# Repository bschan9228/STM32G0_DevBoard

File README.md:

# STM32G0 DevBoard
The STM32G0 DevBoard is a devlopment board based on the STM32G070CBT6. It has a USB Type C connector that only supports power and ST-LINK to program the device. It also contains buttons, LEDs, an external oscillator, and a linear regulator.

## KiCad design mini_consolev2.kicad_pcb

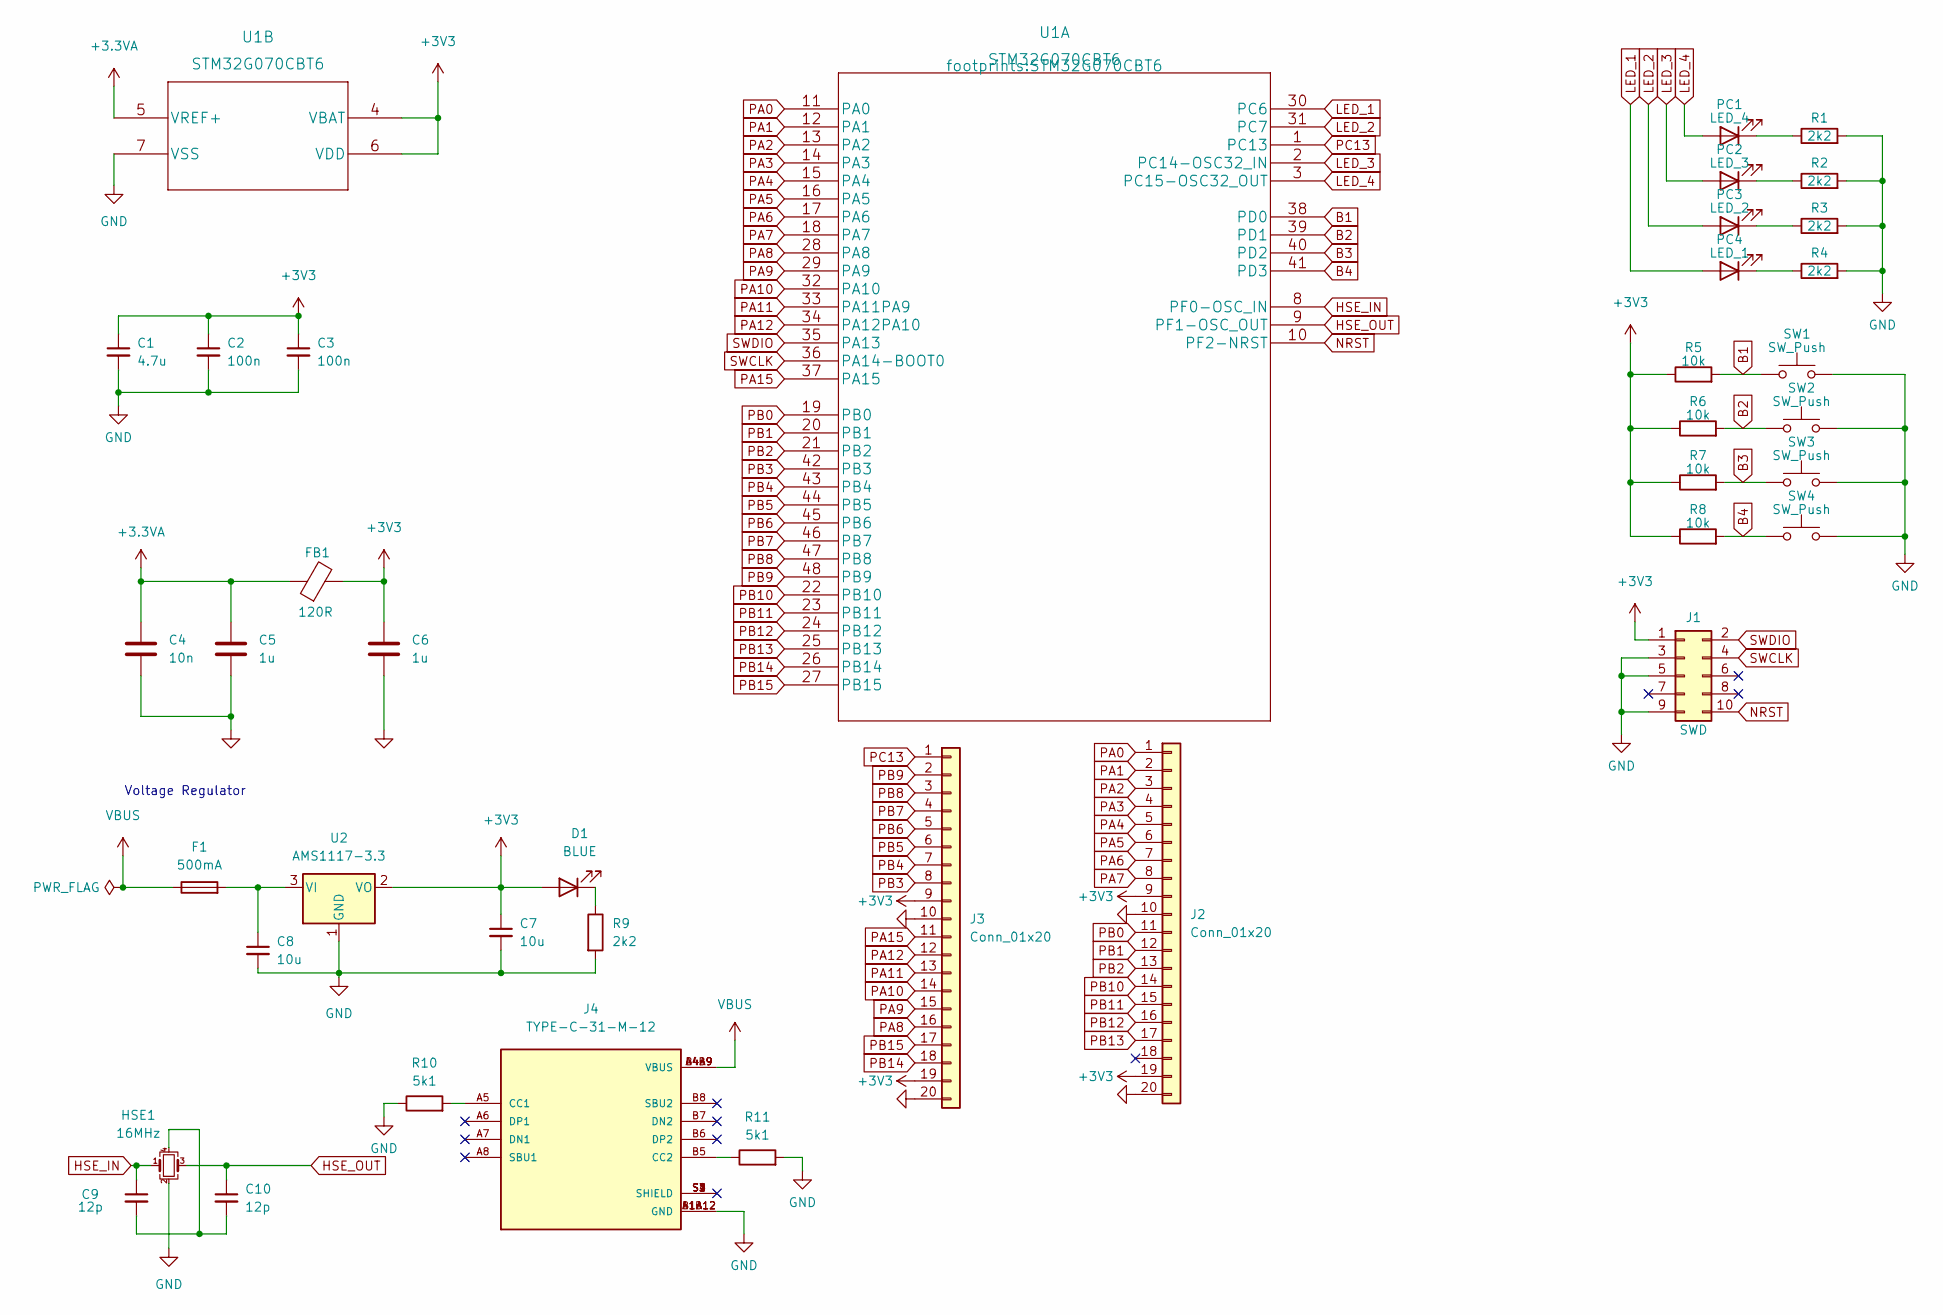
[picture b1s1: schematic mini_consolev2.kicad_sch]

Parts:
C1: 4.7u; C_0603_1608Metric
C2, C3: 100n; C_0402_1005Metric
C4: 10n; C_0402_1005Metric
C5, C6: 1u; C_0402_1005Metric
C7, C8: 10u; C_0603_1608Metric
C9, C10: 12p; C_0402_1005Metric
D1: BLUE; LED_0603_1608Metric
F1: 500mA; Fuse_0603_1608Metric
FB1: 120R; L_0603_1608Metric
HSE1: 16MHz; Crystal_SMD_3225-4Pin_3.2x2.5mm
J1: SWD; PinHeader_2x05_P2.54mm_Vertical
J2, J3: Conn_01x20; PinHeader_1x20_P1.27mm_Vertical
J4: TYPE-C-31-M-12; HRO_TYPE-C-31-M-12; PARTREV A
PC1: LED_4; LED_0603_1608Metric
PC2: LED_3; LED_0603_1608Metric
PC3: LED_2; LED_0603_1608Metric
PC4: LED_1; LED_0603_1608Metric
R1, R2, R3, R4, R9: 2k2; R_0402_1005Metric
R5, R6, R7, R8: 10k; R_0402_1005Metric
R10, R11: 5k1; R_0402_1005Metric
SW1, SW2, SW3, SW4: SW_Push; SW_PUSH_6mm_H5mm
U1: STM32G070CBT6
U2: AMS1117-3.3; SOT-223-3_TabPin2

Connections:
+3.3VA: C4.1, C5.1, FB1.1, U1.5 (VREF+)
+3V3: C1.1, C2.1, C3.1, C6.1, C7.1, D1.2 (A), FB1.2, J1.1, J2.9, J2.19, J3.9, J3.19, R5.1, R6.1, R7.1, R8.1, U1.4 (VBAT), U1.6 (VDD), U2.2 (VO)
B1: R5.2, SW1.1, U1.38 (PD0)
B2: R6.2, SW2.1, U1.39 (PD1)
B3: R7.2, SW3.1, U1.40 (PD2)
B4: R8.2, SW4.1, U1.41 (PD3)
GND: C1.2, C2.2, C3.2, C4.2, C5.2, C6.2, C7.2, C8.2, HSE1.2, J1.3, J1.5, J1.9, J2.10, J2.20, J3.10, J3.20, J4.A1B12 (GND), J4.B1A12 (GND), R1.2, R2.2, R3.2, R4.2, R9.2, R10.1, R11.2, SW1.2, SW2.2, SW3.2, SW4.2, U1.7 (VSS), U2.1 (GND)
HSE_IN: C9.1, HSE1.1, U1.8 (PF0-OSC_IN)
HSE_OUT: C10.1, HSE1.3, U1.9 (PF1-OSC_OUT)
LED_1: PC4.2 (A), U1.30 (PC6)
LED_2: PC3.2 (A), U1.31 (PC7)
LED_3: PC2.2 (A), U1.2 (PC14-OSC32_IN)
LED_4: PC1.2 (A), U1.3 (PC15-OSC32_OUT)
NRST: J1.10, U1.10 (PF2-NRST)
unnamed: C8.1, F1.2, U2.3 (VI)
unnamed: C9.2, C10.2, HSE1.4
unnamed: D1.1 (K), R9.1
unnamed: J4.A5 (CC1), R10.2
unnamed: J4.B5 (CC2), R11.1
unnamed: PC1.1 (K), R1.1
unnamed: PC2.1 (K), R2.1
unnamed: PC3.1 (K), R3.1
unnamed: PC4.1 (K), R4.1
PA0: J2.1, U1.11 (PA0)
PA1: J2.2, U1.12 (PA1)
PA2: J2.3, U1.13 (PA2)
PA3: J2.4, U1.14 (PA3)
PA4: J2.5, U1.15 (PA4)
PA5: J2.6, U1.16 (PA5)
PA6: J2.7, U1.17 (PA6)
PA7: J2.8, U1.18 (PA7)
PA8: J3.16, U1.28 (PA8)
PA9: J3.15, U1.29 (PA9)
PA10: J3.14, U1.32 (PA10)
PA11: J3.13, U1.33 (PA11PA9)
PA12: J3.12, U1.34 (PA12PA10)
PA15: J3.11, U1.37 (PA15)
PB0: J2.11, U1.19 (PB0)
PB1: J2.12, U1.20 (PB1)
PB2: J2.13, U1.21 (PB2)
PB3: J3.8, U1.42 (PB3)
PB4: J3.7, U1.43 (PB4)
PB5: J3.6, U1.44 (PB5)
PB6: J3.5, U1.45 (PB6)
PB7: J3.4, U1.46 (PB7)
PB8: J3.3, U1.47 (PB8)
PB9: J3.2, U1.48 (PB9)
PB10: J2.14, U1.22 (PB10)
PB11: J2.15, U1.23 (PB11)
PB12: J2.16, U1.24 (PB12)
PB13: J2.17, U1.25 (PB13)
PB14: J3.18, U1.26 (PB14)
PB15: J3.17, U1.27 (PB15)
PC13: J3.1, U1.1 (PC13)
SWCLK: J1.4, U1.36 (PA14-BOOT0)
SWDIO: J1.2, U1.35 (PA13)
VBUS: F1.1, J4.A4B9 (VBUS), J4.B4A9 (VBUS)

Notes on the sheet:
Voltage Regulator

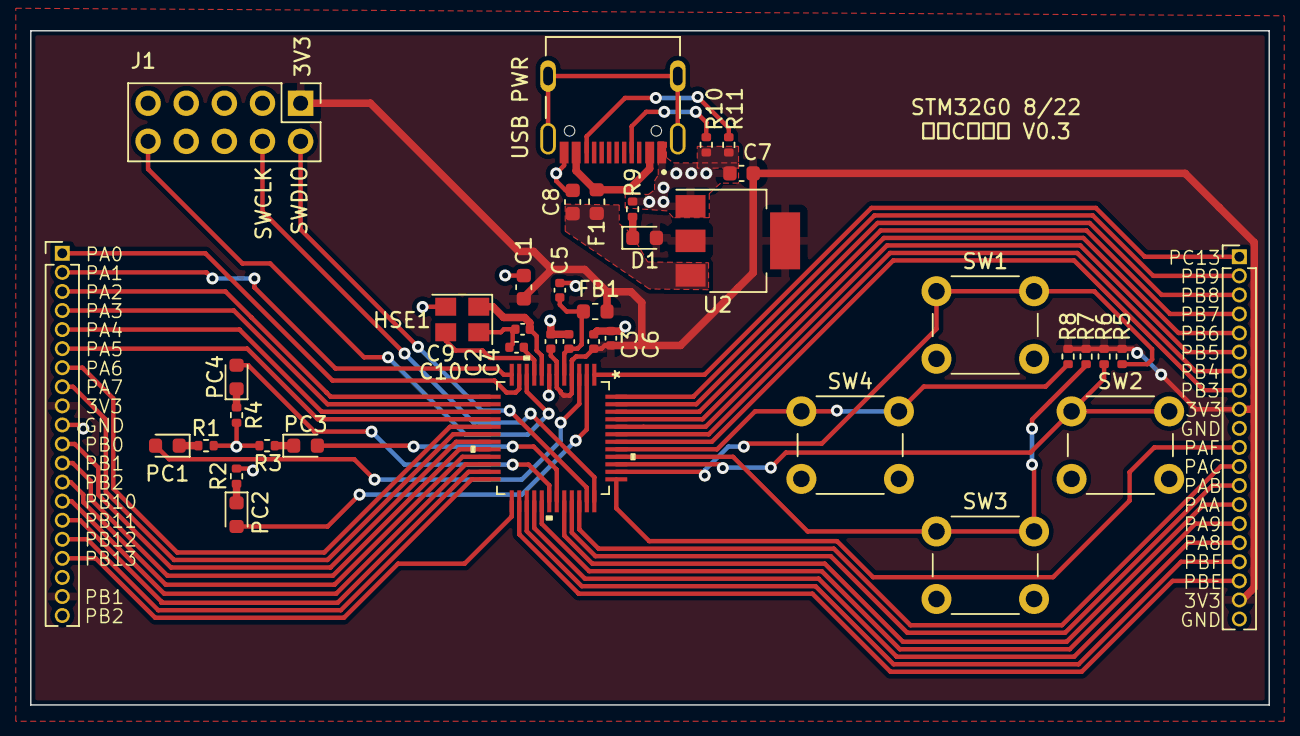
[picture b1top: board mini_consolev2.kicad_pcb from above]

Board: 2 copper layers, 82.5 x 44.9 mm, 39 parts (0 on the bottom side), 57 nets.

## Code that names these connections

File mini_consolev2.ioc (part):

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Mcu.Name=STM32G070CBTx
Mcu.Package=LQFP48
Mcu.UserName=STM32G070CBTx
PA13.Mode=Serial_Wire
PA13.Signal=SYS_SWDIO
PA14-BOOT0.Mode=Serial_Wire
PA14-BOOT0.Signal=SYS_SWCLK
PC14-OSC32_IN\ (PC14).Signal=GPIO_Output
PC15-OSC32_OUT\ (PC15).Signal=GPIO_Output
PC6.Signal=GPIO_Output
PC7.Signal=GPIO_Output
PD0.Signal=GPIO_Input
PD1.Signal=GPIO_Input
PD2.Signal=GPIO_Input
PD3.Signal=GPIO_Input
PF0-OSC_IN\ (PF0).Mode=HSE-External-Oscillator
PF0-OSC_IN\ (PF0).Signal=RCC_OSC_IN
PF1-OSC_OUT\ (PF1).Mode=HSE-External-Oscillator
PF1-OSC_OUT\ (PF1).Signal=RCC_OSC_OUT
RCC.HSE_VALUE=8000000
RCC.SYSCLKFreq_VALUE=16000000
board=custom

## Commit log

2022-08-26 Fixed usbc port

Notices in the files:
parts and their libraries:
Copyright 2021 Accelerated Designs. All rights reserved.
